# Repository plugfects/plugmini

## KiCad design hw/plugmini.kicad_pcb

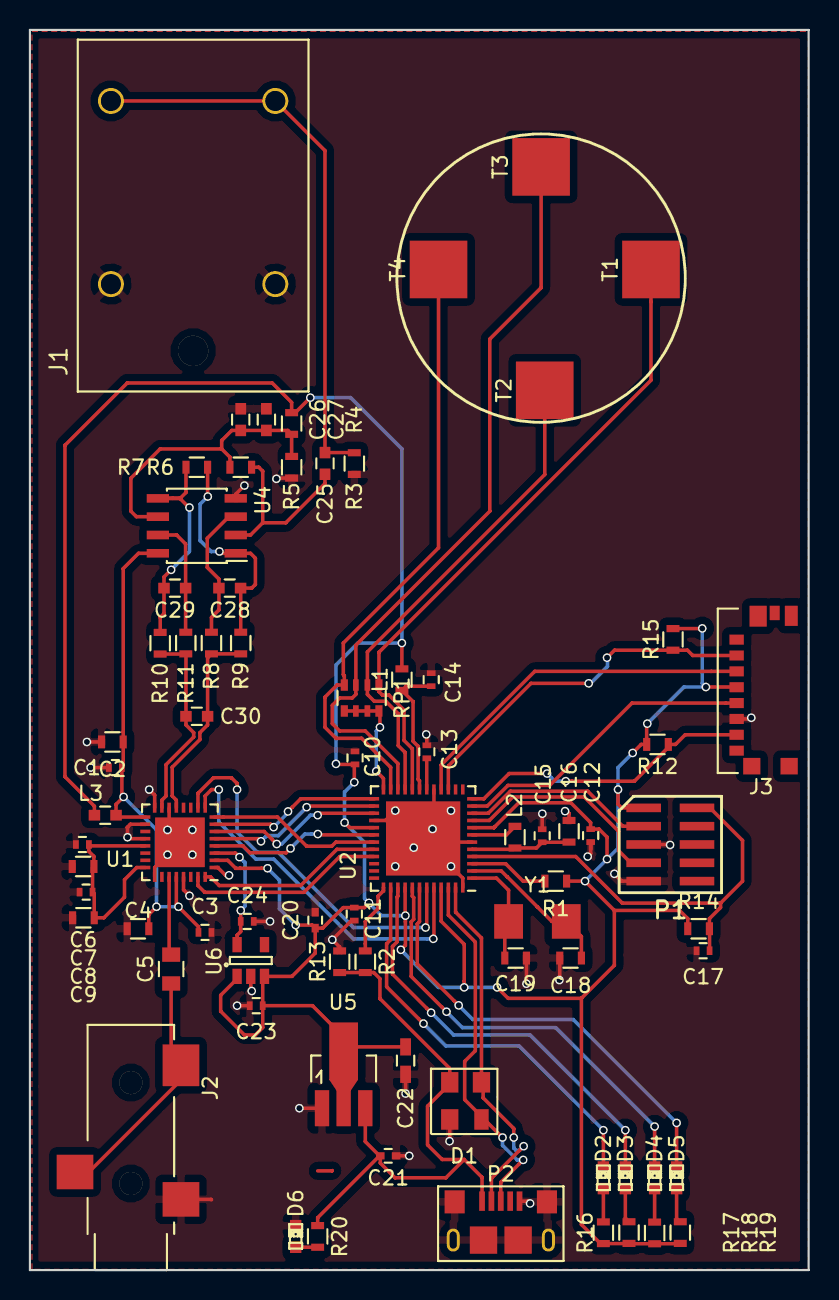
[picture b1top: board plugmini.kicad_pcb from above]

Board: 2 copper layers, 54.0 x 86.0 mm, 75 parts (0 on the bottom side), 59 nets.

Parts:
C1, C3, C6, C8, C10, C11, C12, C13, C14, C15, C17, C23, C24: 0.1uF; R_0402
C2, C4: 10uF; R_0603
C5: 47uF; C_0805
C7, C9: 22uF; R_0603
C16: 4.7uF; R_0603
C18, C19: 22pF; R_0603
C20, C21: 0.1u; C_0402
C22: 10u; C_0603_HandSoldering
C25: 1uF; C_0603
C26: 10nF; C_0603
C27: 100uF; C_0603
C28, C29: 470pF (C0G); C_0603
C30: 2700pF (C0G); C_0603
D1: PRTR5V0U2X; SOT143B
D2, D3, D4, D5, D6: Led_Small; LED-0603
J1: AudioJackMono4p; Jack6.35mm
J2: AudioJackStereo; audio_jack3.5mm
J3: MicroSDCard; sdcard_pushpull
L1: ferrite; R_0603
L2: 22uH; R_0603
L3: L_Small; C_0603
P1: CONN_02X05; CMxDBG
P2: USB_OTG; USB_Micro-B101181930001LF
R1, R12, R15: 10k; R_0603
R2: 820k; R_0603
R3, R4, R5, R6: 100k; R_0603
R7, R8, R10: 634R; R_0603
R9, R11: 91R; R_0603
R13: 1M; R_0603
R14, R16, R17, R18, R19, R20: 1k; R_0603
RP1: R_PACK4; R_Array_Convex_4x0603
T1, T2, T3, T4: touchkey
U1: tlv320aic3120; QFN-32-1EP_5x5mm_Pitch0.5mm
U2: ATSAM4LS; QFN-48-1EP_7x7mm_Pitch0.5mm
U4: LME49721; SOIC-8_3.9x4.9mm_Pitch1.27mm
U5: AZ1117C; SOT89-3_Housing_Handsoldering
U6: TLV71318; SOT-23-5
Y1: 16MHz; 2SMD

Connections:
+3.3VDAC: C1.1, C2.1, C3.1, C4.1, L3.2, U1.17, U1.28, U4.8
/CapacitiveUI/DIS: RP1.5, RP1.6, RP1.7, RP1.8, U2.24
/Processor/CATB4: RP1.1, T1.1, U2.20
/Processor/CATB5: RP1.2, T2.1, U2.21
/Processor/CATB6: RP1.3, T3.1, U2.22
/Processor/CATB7: RP1.4, T4.1, U2.23
/Processor/CODEC_IO: U1.32, U2.32
/Processor/CODEC_RST: U1.31, U2.33
/Processor/D+: D1.3, P2.2, U2.47
/Processor/D-: D1.2, P2.3, U2.46
/Processor/ISMK: U1.8, U2.31
/Processor/ISWS: U1.6, U2.27
/Processor/LED0: D2.1, U2.38
/Processor/LED1: D3.1, U2.39
/Processor/LED2: D4.1, U2.41
/Processor/LED3: D5.1, U2.42
/Processor/MISO: J3.7, R12.2, U2.12
/Processor/MOSI: J3.3, U2.16
/Processor/SCL: U1.10, U2.43
/Processor/SDA: U1.9, U2.44
/Processor/SPI_CLK: J3.5, U2.11
/Processor/SWD_CLK: P1.4, U2.9
/Processor/SWD_DIO: P1.2, U2.10
/Processor/VDDCORE: C15.1, C16.1, L2.1, U2.5
/Processor/VREF: C13.1, U2.18
/Processor/~RESET: C17.1, P1.10, R14.2, U2.4
/Processor/~SS: J3.2, R15.2, U2.15
/Sheet57346A80/AUDIO_IN_N: C30.2, R10.1, R11.2, U1.15
/Sheet57346A80/AUDIO_IN_P: C30.1, R8.1, R9.1, U1.13
/Sheet57346997/BCLK: U1.7, U2.25
/Sheet57346997/DIN: U1.5, U2.26
/Sheet57346997/DOUT: U1.4, U2.30
/Sheet57346997/HPOUT: C5.2, J2.1, J2.2
/Sheet57346997/SPKM: U1.19, U1.23
/Sheet57346997/SPKP: U1.22, U1.26
/Sheet57346997/SPKVDD: C6.1, C7.1, C8.1, C9.1, U1.21, U1.24
GND: C1.2, C2.2, C3.2, C4.2, C6.2, C7.2, C8.2, C9.2, C10.2, C11.2, C12.2, C13.2, C14.2, C15.2, C16.2, C17.2, C18.2, C19.2, C20.2, C21.2, C22.2, C23.2, C24.2, C26.2, C27.2, D1.1, D6.1, J1.3, J1.6, J2.3, J3.6, P1.3, P1.5, P2.5, P2.6, R3.1, R5.1, R13.2, U1.1, U1.14, U1.16, U1.18, U1.20, U1.25, U1.29, U1.33, U2.6, U2.17, U2.28, U2.48, U2.49, U4.4, U5.1, U6.2
unnamed: C5.1, U1.27
unnamed: C18.1, U2.2, Y1.1
unnamed: C19.1, U2.1, Y1.2
unnamed: C24.1, U1.3, U6.5
unnamed: C25.1, R6.2, U4.2
unnamed: C25.2, J1.1, J1.4, R3.2
unnamed: C26.1, C27.1, R4.1, R5.2, R6.1, U4.6
unnamed: C28.1, R7.1, R9.2, U4.1
unnamed: C28.2, R8.2, U4.3
unnamed: C29.1, R7.2, R10.2, U4.5
unnamed: C29.2, R11.1, U4.7
unnamed: D2.2, R16.2
unnamed: D3.2, R17.2
unnamed: D4.2, R18.2
unnamed: D5.2, R19.2
unnamed: D6.2, R20.2
unnamed: L2.2, U2.7
unnamed: R1.2, U2.3
unnamed: R2.1, U2.37
VAA: C14.1, L1.2, U2.19
VCC: C21.1, D1.4, P2.1, R2.2, R13.1, R20.1, U5.3
VDD: C10.1, C11.1, C12.1, C20.1, C22.1, C23.1, J3.4, L1.1, L3.1, P1.1, R1.1, R4.2, R12.1, R14.1, R15.1, R16.1, R17.1, R18.1, R19.1, U1.2, U2.8, U2.29, U2.40, U2.45, U5.2, U6.1, U6.3

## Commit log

2016-05-14 First circuits
2016-05-14 Update microcontroller circuit
2016-05-19 Added fw start with ceedling as build system
2016-05-20 layout modifications
2016-05-24 Layout updates
2016-06-04 Version 0.1. No BLE, no cap touch and 4 layers
2016-06-12 Added few leds and cap pads
